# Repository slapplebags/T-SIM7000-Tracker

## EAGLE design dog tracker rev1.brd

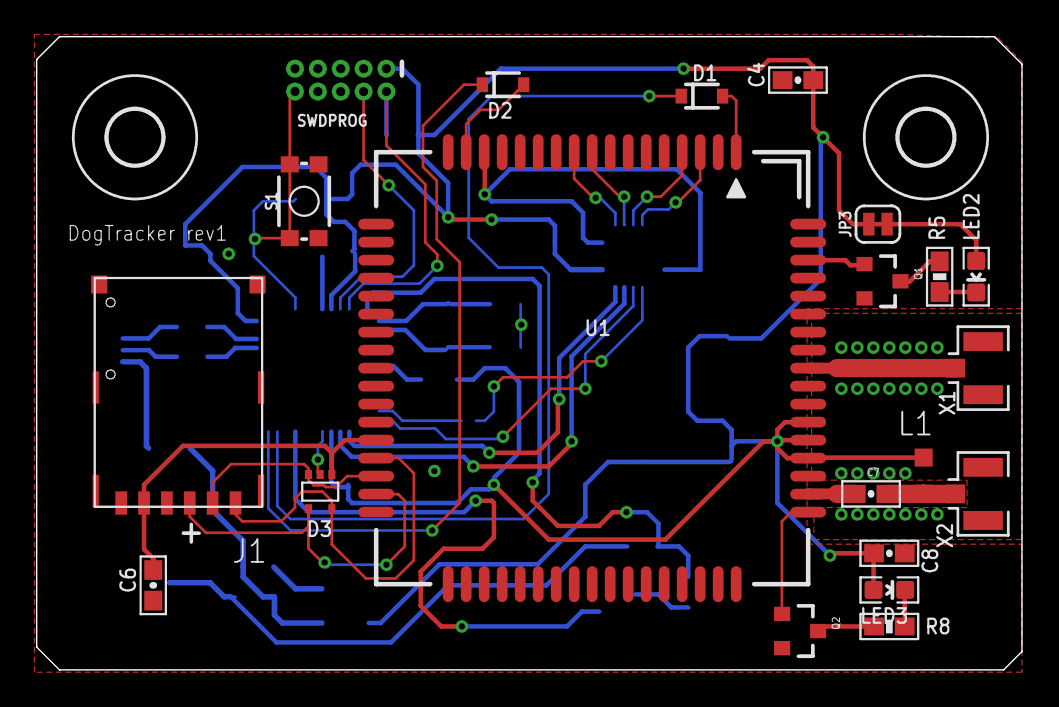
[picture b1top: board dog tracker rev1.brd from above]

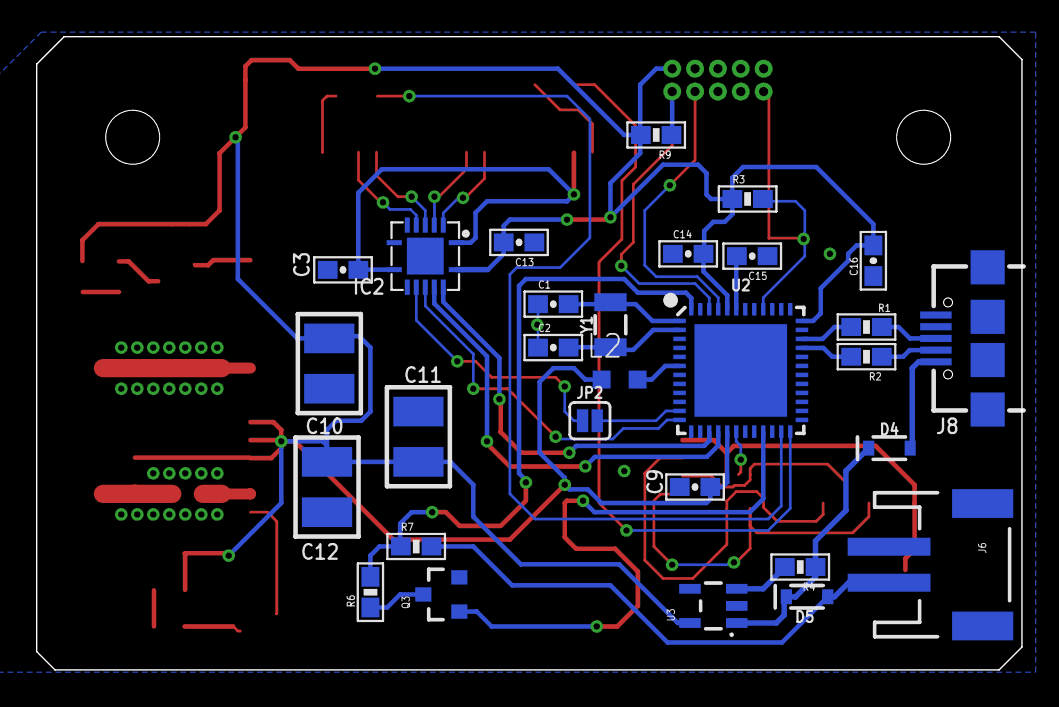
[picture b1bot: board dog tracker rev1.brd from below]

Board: 2 copper layers, 54.7 x 35.2 mm, 52 parts (29 on the bottom side), 48 nets.

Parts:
C1, C2: 22pF; 0603-CAP-MARKED
C3, C4, C8, C13, C14, C15, C16: 0.1uF; 0603-CAP-MARKED
C6: 0.22uF; 0603-CAP-MARKED
C7: 33pF; 0603-CAP-MARKED
C9: 1uF; 0603-CAP-MARKED
C10, C11, C12: 100uF; 1210
D1, D2: 250mA/100V; SOD-323
D3: MSQA6V1W5T2G; SOT-353
D4, D5: 1A/23V/620mV; SOD-323
H1, H2: MOUNT-HOLE3.0; 3,0
IC2: TXB0104; VQFN-14
J1: 693043020611
J6: LiPo; JST-2-SMD
J8: microUSB; USB-B-MICRO-SMD
JP2: SMT-JUMPER_2_NO_SILK
JP3: SMT-JUMPER_2_NC_TRACE_SILK
L1, L2: 27nh; L2012C
LED2: Green; LED-0603-MARKED
LED3: Blue; LED-0603-MARKED
Q1, Q2, Q3: BSS138L; SOT23-3
R1, R2, R4: 22; 0603-RES-MARKED
R3, R7, R9: 10k; 0603-RES-MARKED
R5: 2k; 0603-RES-MARKED
R6: 30k; 0603-RES-MARKED
R8: 470; 0603-RES-MARKED
S1: Reset; TACTILE_SWITCH_SMD_4.6X2.8MM
SWDPROG: CORTEX_DEBUG_PTH; 2X5-PTH-1.27MM
U1: SIM7000
U2: ATSAMD21G-M; QFN-48
U3: 3.3V; SOT23-5
X1: LTE-uFL; U.FL
X2: GNSS-uFL; U.FL
Y1: 32.768kHz; CRYSTAL-SMD-3.2X1.5MM

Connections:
1.8V: C3.2, IC2.1, IC2.8, U1.15
3.3V: C4.1, C8.1, C9.1, C10.1, C11.1, C12.1, C13.2, C14.2, C16.2, IC2.14, JP3.1, L1.1, L2.1, LED3.A, R3.1, R9.2, SWDPROG.1, U1.55, U1.56, U1.57, U2.17, U2.36, U2.44, U3.5
!RESET: R3.2, S1.3, S1.4, SWDPROG.10, U2.40
BATT_SENSE: R6.2, R7.1, U2.48
D+: J8.D+, R1.1
D-: J8.D-, R2.1
GND: C1.1, C2.1, C3.1, C4.2, C6.2, C8.2, C9.2, C10.2, C11.2, C12.2, C13.1, C14.1, C15.1, C16.1, D3.2, IC2.7, IC2.PAD, J1.C5, J1.Z1, J1.Z2, J1.Z3, J6.1, J8.GND, J8.SHIELD1, J8.SHIELD2, J8.SHIELD3, J8.SHIELD4, Q1.2, Q2.2, Q3.2, S1.1, S1.2, SWDPROG.3, SWDPROG.5, SWDPROG.9, U1.2, U1.17, U1.18, U1.29, U1.39, U1.45, U1.46, U1.54, U1.58, U1.59, U1.61, U1.62, U1.63, U1.64, U1.65, U2.5, U2.18, U2.35, U2.42, U3.2, X1.1, X1.2, X2.1, X2.2
LTE_DTR: IC2.5, U1.3
LTE_PWR: D1.C, U2.23
LTE_RI: IC2.4, U1.4
LTE_RST: D2.C, U2.24
LTE_RXD: IC2.2, U1.10
LTE_TXD: IC2.3, U1.9
unnamed: C7.2, U1.53
unnamed: D1.A, U1.1
unnamed: C7.1, L1.2, X2.3
unnamed: Q1.3, R5.1
unnamed: LED2.C, R5.2
unnamed: C2.2, U2.2, Y1.P$1
unnamed: C1.2, U2.1, Y1.P$2
unnamed: JP2.1, U2.11
unnamed: R2.2, U2.33
unnamed: Q2.3, R8.1
unnamed: LED3.C, R8.2
unnamed: JP3.2, LED2.A
unnamed: R1.2, U2.34
unnamed: Q3.3, R6.1
unnamed: C15.2, U2.43
unnamed: R4.2, U3.3
unnamed: D4.C, D5.C, R4.1, U3.1
NETLIGHT: Q2.1, U1.52
NRESET: D2.A, U1.16
PWR_STAT: Q1.1, U1.66
RF_ANT: U1.60, X1.3
SENSE_GATE: Q3.1, U2.21
SIM_CLK: D3.3, J1.C3, U1.32
SIM_DATA: D3.5, J1.C7, U1.31
SIM_RST: D3.4, J1.C2, U1.33
SIM_VCC: C6.1, D3.1, J1.C1, U1.30
SWCLK: SWDPROG.4, U2.45
SWDIO: R9.1, SWDPROG.2, U2.46
UC_DTR: IC2.10, JP2.2
UC_RI: IC2.11, U2.12
UC_RXD: IC2.12, U2.16
UC_TXD: IC2.13, U2.15
VDDANA: L2.2, U2.6
V_BATT: D5.A, J6.2, R7.2
V_USB: D4.A, J8.VBUS

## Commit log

2020-11-14 basics working with google FI and dweet
2020-11-14 added trimmed down dog tracker sketch with mostly only required items. tested and working
2020-11-18 now able to get dweet and run code based on json content.
2020-11-18 fixed dog tracker and added deep sleep
2020-11-19 starting over on dog tracker, should be less fucky now
2020-11-19 base features implemented, need cleep and cleanup.
2020-11-20 added and testing sleep.
2020-11-20 sleep tested and cleanup completed.
2020-11-22 first PCB rev, minor fixes to software
2020-11-22 first PCB rev1 fixes
2020-11-22 rev1 fixed and sent to fab
2020-11-22 rev1 fixed sim card holder / reset button clearance issue
2020-11-22 rev1 resolved other minor issues, added battery sense, routed all power through LDO and added diode mixing to power input.
2021-01-09 rev1.1
    fixed USB and serial connections

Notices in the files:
parts and their libraries:
SparkFun-IC-Microcontroller: Licensing: Creative Commons ShareAlike 4.0 International - https://creativecommons.org/licenses/by-sa/4.0
Wurth_Elektronik_Electromechanic_Input-O: Copyright: Würth Elektronik
